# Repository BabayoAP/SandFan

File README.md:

# SandFan

My project for Half-Life by Hack Club!

Meant for climbers, a two-in-one portable device:
 - Variable speed enclosed fan for drying out wet hands on one side.
 - Variable speed skin-sander for grinding down overgrown calluses.

No firmware: analog design, no microcontroller.

## Schematic and board

## Bill of materials

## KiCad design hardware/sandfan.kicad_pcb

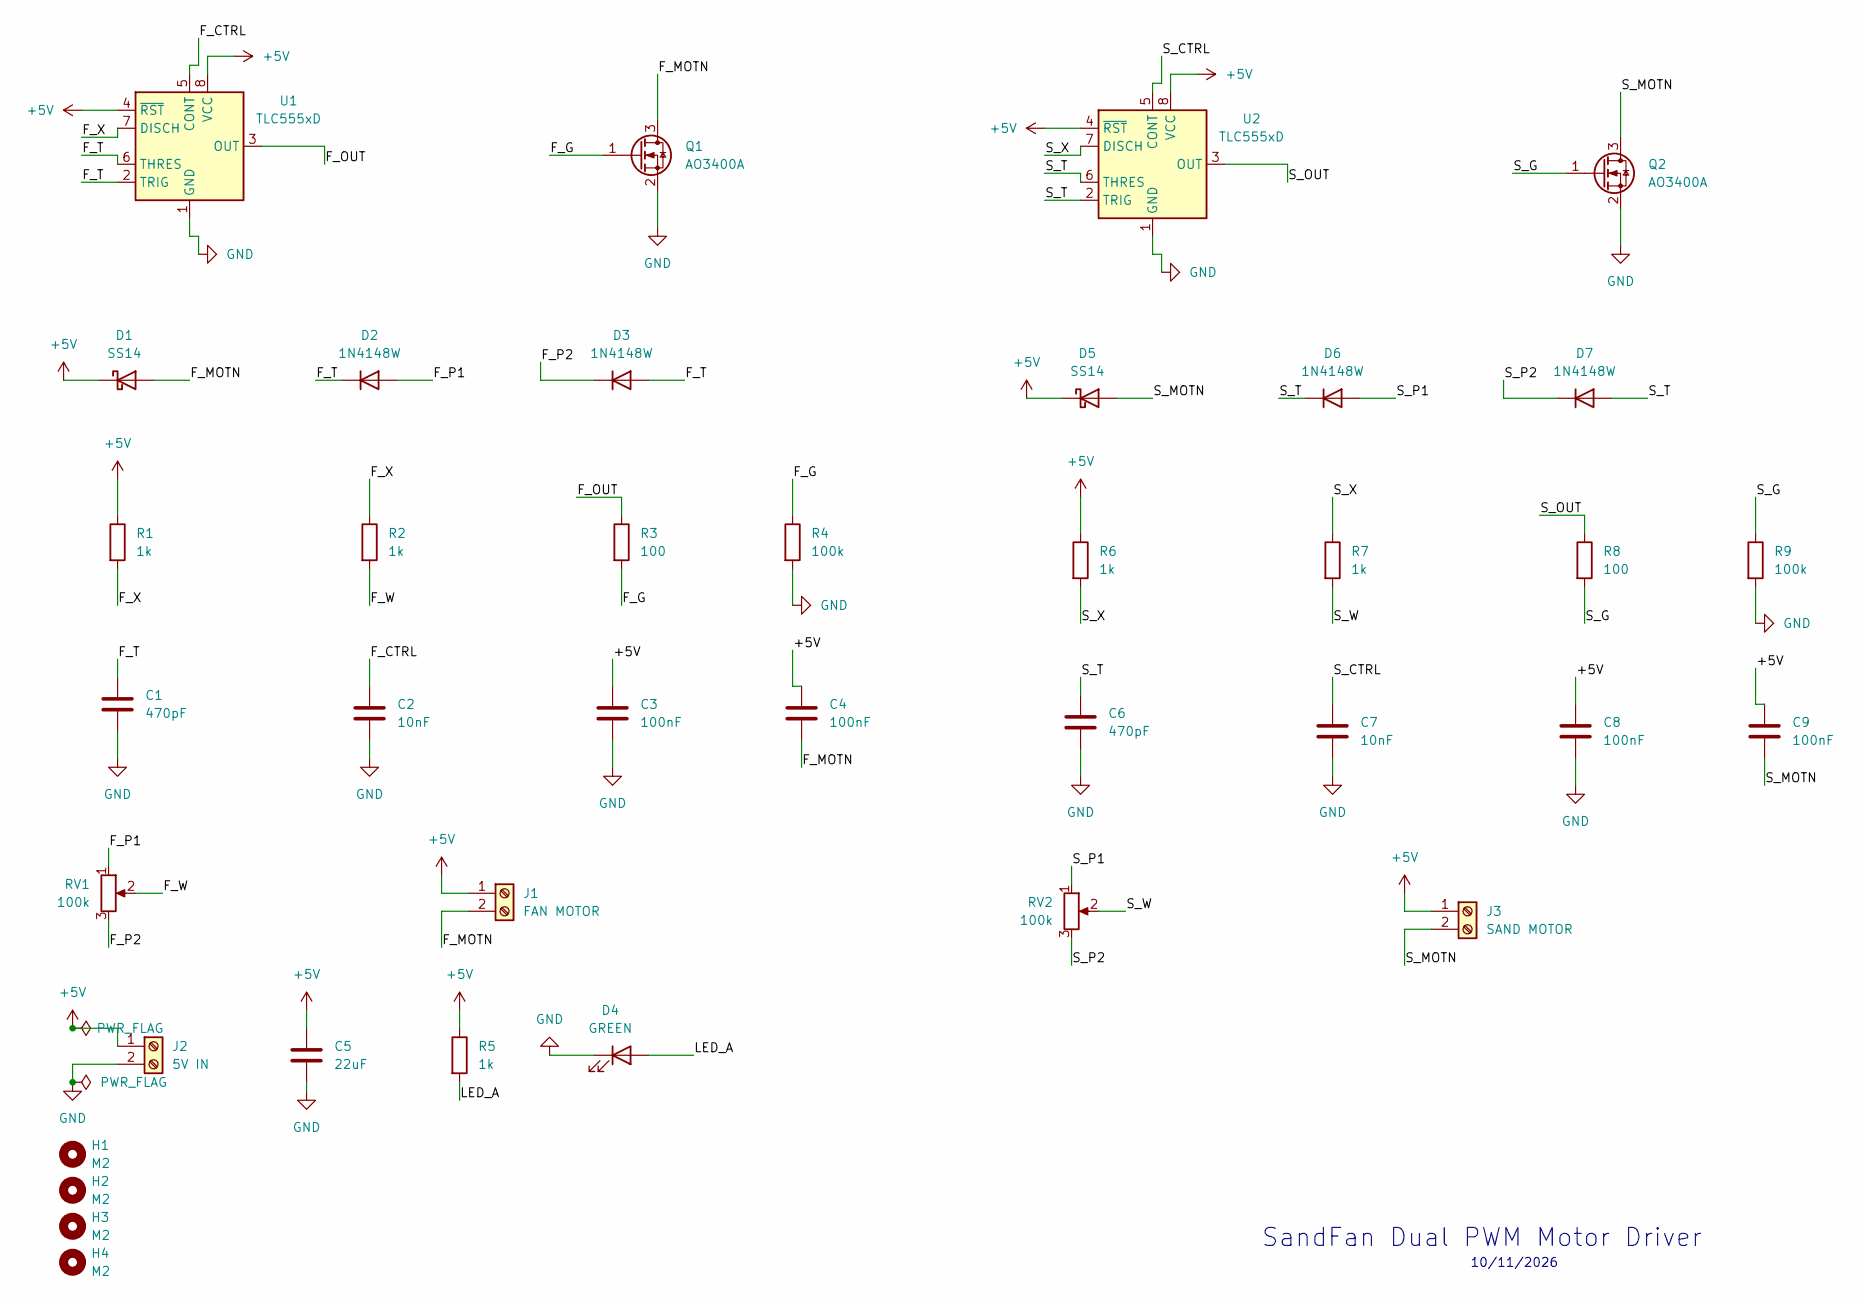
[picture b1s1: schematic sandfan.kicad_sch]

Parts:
C1, C6: 470pF; C_0805_2012Metric
C2, C7: 10nF; C_0805_2012Metric
C3, C4, C8, C9: 100nF; C_0805_2012Metric
C5: 22uF; C_0805_2012Metric
D1, D5: SS14; D_SMA
D2, D3, D6, D7: 1N4148W; D_SOD-123
D4: GREEN; LED_0805_2012Metric
H1, H2, H3, H4: M2; MountingHole_2.2mm_M2_DIN965
J1: FAN MOTOR; TerminalBlock_Phoenix_MKDS-1,5-2-5.08_1x02_P5.08mm_Horizont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
J2: 5V IN; TerminalBlock_Phoenix_MKDS-1,5-2-5.08_1x02_P5.08mm_Horizont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
J3: SAND MOTOR; TerminalBlock_Phoenix_MKDS-1,5-2-5.08_1x02_P5.08mm_Horizont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
Q1, Q2: AO3400A; SOT-23
R1, R2, R5, R6, R7: 1k; R_0805_2012Metric
R3, R8: 100; R_0805_2012Metric
R4, R9: 100k; R_0805_2012Metric
RV1, RV2: 100k; Potentiometer_Bourns_PTV09A-1_Single_Vertical
U1, U2: TLC555xD; SOIC-8_3.9x4.9mm_P1.27mm

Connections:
+5V: C3.1, C4.1, C5.1, C8.1, C9.1, D1.1 (K), D5.1 (K), J1.1, J2.1, J3.1, R1.1, R5.1, R6.1, U1.4 (~RST), U1.8 (VCC), U2.4 (~RST), U2.8 (VCC)
/F_CTRL: C2.1, U1.5 (CONT)
/F_G: Q1.1 (G), R3.2, R4.1
/F_MOTN: C4.2, D1.2 (A), J1.2, Q1.3 (D)
/F_OUT: R3.1, U1.3 (OUT)
/F_P1: D2.2 (A), RV1.1
/F_P2: D3.1 (K), RV1.3
/F_T: C1.1, D2.1 (K), D3.2 (A), U1.2 (TRIG), U1.6 (THRES)
/F_W: R2.2, RV1.2
/F_X: R1.2, R2.1, U1.7 (DISCH)
/LED_A: D4.2 (A), R5.2
/S_CTRL: C7.1, U2.5 (CONT)
/S_G: Q2.1 (G), R8.2, R9.1
/S_MOTN: C9.2, D5.2 (A), J3.2, Q2.3 (D)
/S_OUT: R8.1, U2.3 (OUT)
/S_P1: D6.2 (A), RV2.1
/S_P2: D7.1 (K), RV2.3
/S_T: C6.1, D6.1 (K), D7.2 (A), U2.2 (TRIG), U2.6 (THRES)
/S_W: R7.2, RV2.2
/S_X: R6.2, R7.1, U2.7 (DISCH)
GND: C1.2, C2.2, C3.2, C5.2, C6.2, C7.2, C8.2, D4.1 (K), J2.2, Q1.2 (S), Q2.2 (S), R4.2, R9.2, U1.1 (GND), U2.1 (GND)

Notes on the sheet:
10/11/2026
SandFan Dual PWM Motor Driver

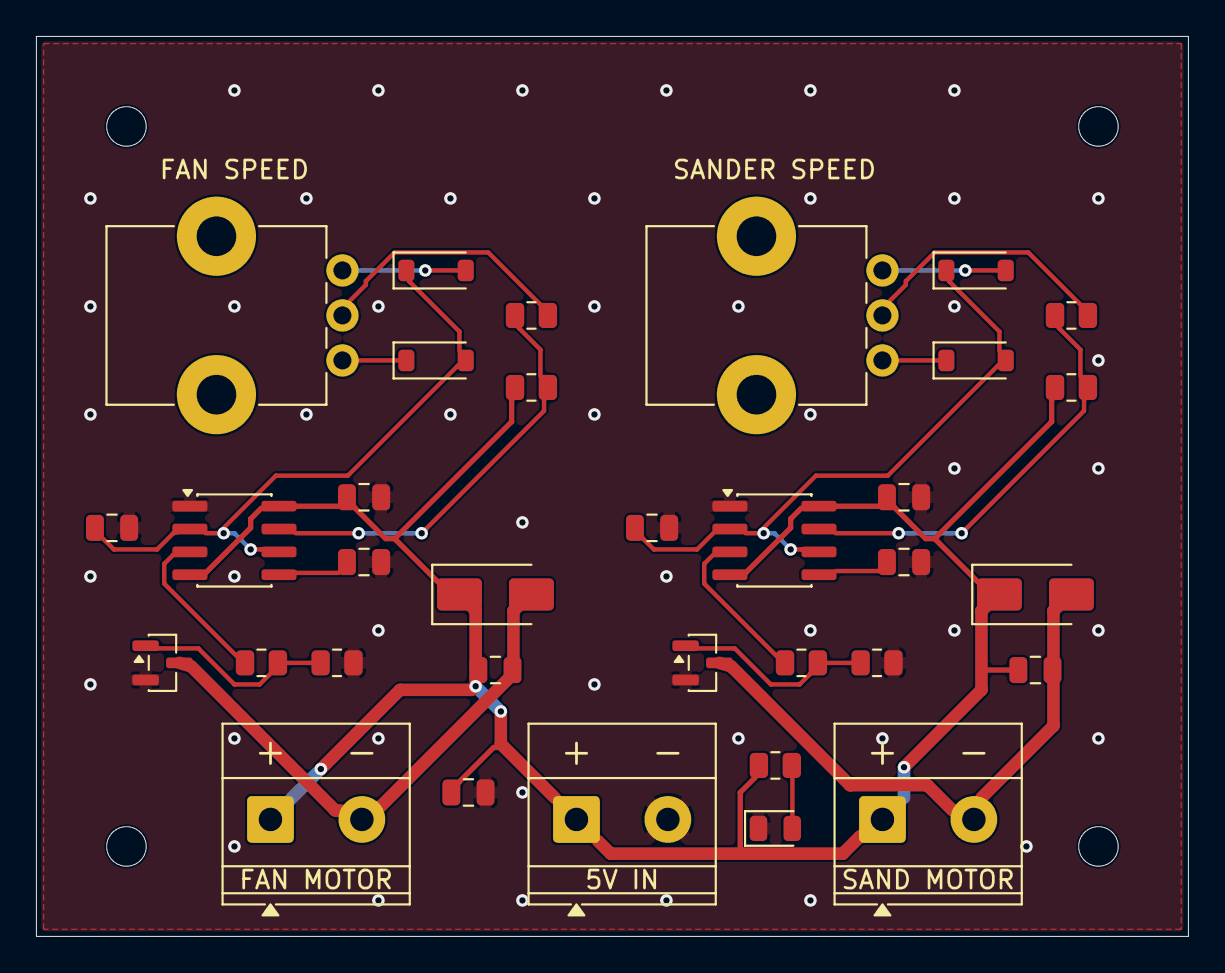
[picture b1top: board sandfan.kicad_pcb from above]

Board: 2 copper layers, 64.0 x 50.0 mm, 38 parts (0 on the bottom side), 21 nets.

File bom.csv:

Designators,Qty,Value,Footprint,Description,Part number,Vendor,Est. unit price (USD),Est. line total (USD),Notes
"U1,U2",2,TLC555,SOIC-8 3.9x4.9mm,CMOS 555 timer (one per motor),TLC555CDR,Digi-Key,0.60,1.20,Digi-Key lists TLC555CD (tube) as discontinued; order the CDR reel/cut-tape part
"Q1,Q2",2,AO3400A,SOT-23,N-channel logic-level MOSFET (motor low-side switch),AO3400A,LCSC (C20917),0.10,0.20,LCSC has minimum order quantities; several clone makers list the same part
"D1,D5",2,SS14,SMA,1 A Schottky flyback diode across each motor,SS14,LCSC / Digi-Key,0.10,0.20,Rated 1 A; check stall current of the real motors
"D2,D3,D6,D7",4,1N4148W,SOD-123,Small-signal steering diode for the PWM duty network,1N4148W-7-F,Digi-Key / LCSC,0.05,0.20,
D4,1,GREEN,LED 0805,Power indicator LED,generic green 0805 LED,LCSC / Digi-Key,0.10,0.10,Pair with R5 (1k)
"RV1,RV2",2,100k,"Bourns PTV09A vertical, 9 mm",Speed pot (fan / sander),PTV09A-4020F-B104,Digi-Key / element14 / RS,1.40,2.80,CHECK: confirm the pin spacing and shaft option of this exact part number against the PTV09A-1 footprint in the datasheet before ordering
"J1,J2,J3",3,2-pos 5.08 mm screw terminal,TerminalBlock_Phoenix_MKDS-1.5-2-5.08,"Fan motor / 5V in / sander motor",MKDS 1.5/2-5.08 (1729128),Farnell / Digi-Key,1.20,3.60,Generic 5.08 mm screw terminals with the same footprint are cheaper if you do not need Phoenix
"R1,R2,R5,R6,R7",5,1k,0805,1% thick-film resistor,RC0805FR-071KL,Digi-Key / LCSC,0.02,0.10,R5 is the LED resistor
"R3,R8",2,100,0805,1% thick-film resistor (MOSFET gate),RC0805FR-07100RL,Digi-Key / LCSC,0.02,0.04,
"R4,R9",2,100k,0805,1% thick-film resistor (MOSFET gate pulldown),RC0805FR-07100KL,Digi-Key / LCSC,0.02,0.04,
"C1,C6",2,470pF,0805,C0G/NP0 50 V timing capacitor,generic 0805 C0G 470pF 50V,Digi-Key / LCSC,0.03,0.06,Use C0G for timing stability
"C2,C7",2,10nF,0805,X7R 50 V 555 control-pin capacitor,generic 0805 X7R 10nF 50V,Digi-Key / LCSC,0.02,0.04,
"C3,C4,C8,C9",4,100nF,0805,X7R 50 V decoupling / motor capacitor,generic 0805 X7R 100nF 50V,Digi-Key / LCSC,0.02,0.08,
C5,1,22uF,0805,X5R 16 V bulk capacitor on the 5V input,generic 0805 X5R 22uF 16V,Digi-Key / LCSC,0.15,0.15,A 10 V part is marginal on a 5 V rail; use 16 V
,,,,,,,Est. parts subtotal,8.81,Unit prices are estimates rounded from distributor listings I could find; none are live quotes. Excludes tax and shipping. Confirm each price at checkout.
